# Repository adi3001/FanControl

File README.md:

# FanControl by CyberPlant

The a sample code for automatic speed control for the fan.
__________

# Description

Is, a compact device with a combination of some simple and useful functions.
The CyberPlant Automatic Fan Control measures temperature via the ds18b20 sensor.
the  temperature  sensor can be installed on the device or any other location
One single sensor can be connected directly to the device itself, or multiple sensors can be connected in series, for more precise ambient temperature reading. 
The CyberPlant Automatic Fan Control has offers smooth adjustments to the fan resolution speed. 
The combination of all the functions offer a precise versatile aid to controlling the temperature.

The fan motor takes its power directly from AC current running at 50Hz or 60Hz.

How does it work?
Setting up the CyberPlant Automatic Fan Control is very simple.

There are only two buttons required to set the programmable options.
With these, we can set the desired temperature values and also the Manual or Automatic Modes.

Automatic Mode.
During automatic mode if the temperature exceeds the set value, the electric charge will pulse every 2 seconds to add momentum.
If the temperature drops below the set value the fan speed will decrease until it stops. 
If the air temperature remains constant no change will occur.

This method allows the device to set the optimal speed for the fan, it prevents the temperature from exceeding the predetermined limit, reducing the total fan revolutions to the minimum possible and thereby saving on power consumption and noise levels.

On Manual Mode.
If you press the two buttons simultaneously the device will enter manual mode.
Here we can manually set the required power to the appliance and the settings are stored in non-volatile memory.
To switch back to automatic mode again just press both buttons simultaneously.

All logical parts are built on the ATmega328 microcontroller running the Arduino IDE. 
The Arduino board provides I2C Pins for connecting the device to other microcontrollers and a 6-pin to USB-TTL for easy program customisation which makes it all a very flexible and easily modifiable.to fit all your needs.
For example, maybe you would like to connect the device to the Internet this is easily done with the Arduino Internet Shield. 

or maybe you want the opposite, to heat the air in the room? It is easy! You can easily change the configuration of the device.

FanControl works with 220V AC and 110V AC at 50 Hz and 60 Hz And allows you to control the current to 4 amperes

It can display temperature in Celsius and Fahrenheit. 

FanControl is a simple and intuitive device with a great potential for modification and expansion. 
Use your imagination and a set of ready-made programs from Arduino IDE can build the automation of your dreams. 
This is an open source project. 

CyberPlant - help to people and love to plants

### Specifications

Temp sensor - DS18B20
Triac - 4A
works with 220V AC and 110V AC at 50 Hz and 60 Hz

[WWW.CYBERPLANT.INFO](http://www.cyberplant.info)

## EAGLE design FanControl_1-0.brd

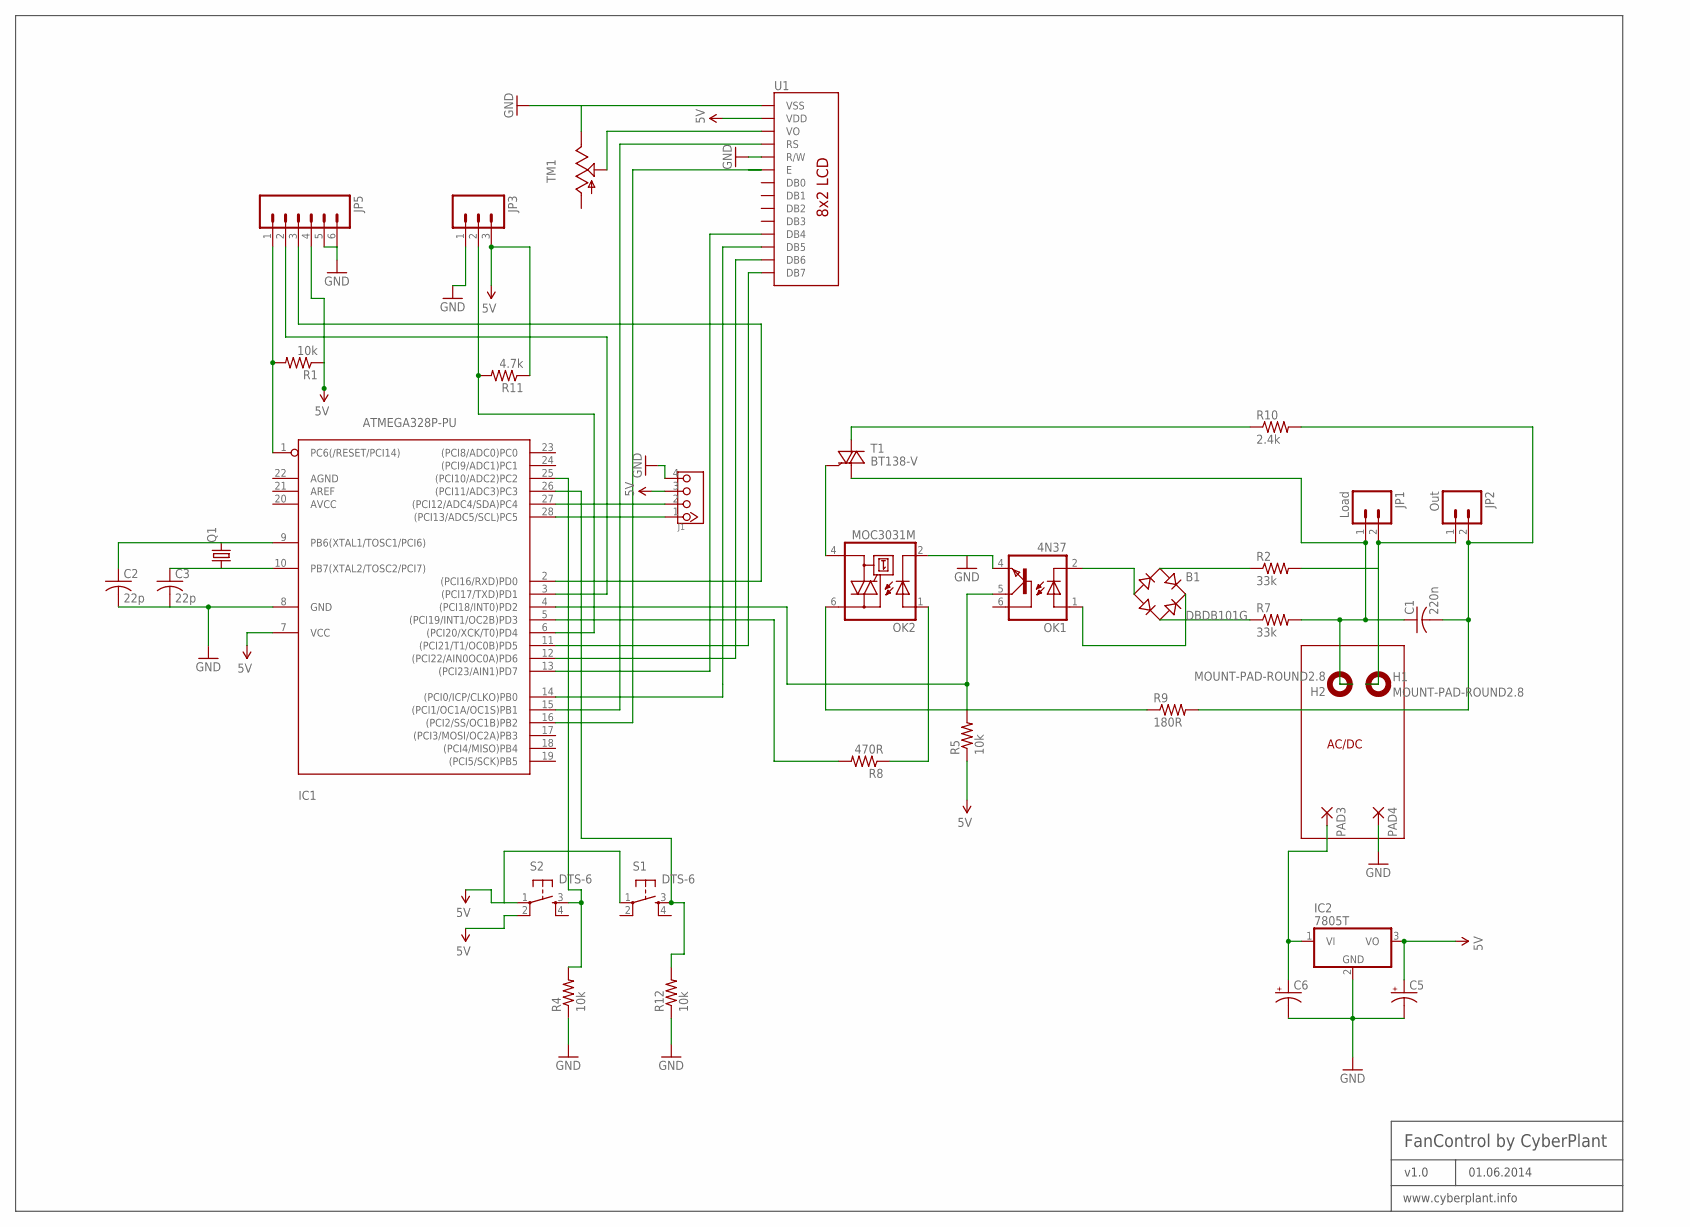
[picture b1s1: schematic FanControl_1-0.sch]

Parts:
B1: DBDB101G; DB
C1: 220n; C150-064X183
C2, C3: 22p; C050-025X075
C5, C6: CAP_POLPTH2; CPOL-RADIAL-10UF-25V
H1, H2: MOUNT-PAD-ROUND2.8; 2,8-PAD
IC1: ATMEGA328P-PU; DIL28-3
IC2: 7805T; TO220H
J1: TWIG-4P-2.090D; 4P-2.0-90D
JP1: Load; SCREWTERMINAL-5MM-2
JP2: Out; SCREWTERMINAL-5MM-2
JP3: M031X03_NO_SILK; 1X03_NO_SILK
JP5: M06SIP; 1X06
OK1: 4N37; DIL06
OK2: MOC3031M; DIL06
PAD3, PAD4: 1,6/0,8
Q1: CRYSTALHC49S; HC49/S
R1, R4, R5, R12: 10k; 1/6W-RES
R2, R7: 33k; AXIAL-0.6
R8: 470R; AXIAL-0.4
R9: 180R; AXIAL-0.8
R10: 2.4k; AXIAL-0.8
R11: 4.7k; AXIAL-0.4
S1, S2: DTS-6
T1: BT138-V; TO220BV
TM1: TRIM; 6MM
U1: LCD-8X2-WH0802A8X2; LCD-8X2-WH0802A

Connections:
5V: C5.1 (+), IC1.7 (VCC), IC2.3 (VO), J1.3, JP3.3, JP5.4, R1.1, R5.1, R11.P$1 (1), S1.1, S2.1, S2.2, U1.2 (VDD)
GND: C2.2, C3.2, C5.2 (-), C6.2 (-), IC1.8 (GND), IC2.2 (GND), J1.4, JP3.1, JP5.5, JP5.6, OK1.4 (EMI), OK2.2 (C), PAD4.1, R4.1, R12.1, TM1.E, U1.1 (VSS), U1.5 (R/W)
unnamed: C1.1, H2.B2,8, JP1.1, R7.P$2 (2), T1.T1 (A1)
unnamed: C1.2, JP2.2, R9.P$2 (2), R10.P$2 (2)
unnamed: H1.B2,8, JP1.2, JP2.1, R2.P$2 (2)
unnamed: B1.AC1, R2.P$1 (1)
unnamed: B1.AC2, R7.P$1 (1)
unnamed: B1.-, OK1.2 (C)
unnamed: B1.+, OK1.1 (A)
unnamed: IC1.4 ((PCI18/INT0)PD2), OK1.5 (COL), R5.2
unnamed: OK2.4 (A1), T1.G
unnamed: IC1.5 ((PCI19/INT1/OC2B)PD3), R8.P$2 (2)
unnamed: OK2.1 (A), R8.P$1 (1)
unnamed: R10.P$1 (1), T1.T2 (A2)
unnamed: OK2.6 (A2), R9.P$1 (1)
unnamed: C2.1, IC1.9 (PB6(XTAL1/TOSC1/PCI6)), Q1.2
unnamed: C3.1, IC1.10 (PB7(XTAL2/TOSC2/PCI7)), Q1.1
unnamed: IC1.6 ((PCI20/XCK/T0)PD4), JP3.2, R11.P$2 (2)
unnamed: C6.1 (+), IC2.1 (VI), PAD3.1
unnamed: TM1.S, U1.3 (VO)
unnamed: IC1.15 ((PCI1/OC1A/OC1S)PB1), U1.4 (RS)
unnamed: IC1.16 ((PCI2/SS/OC1B)PB2), U1.6 (E)
unnamed: IC1.13 ((PCI23/AIN1)PD7), U1.11 (DB4)
unnamed: IC1.14 ((PCI0/ICP/CLKO)PB0), U1.12 (DB5)
unnamed: IC1.12 ((PCI22/AIN0OC0A)PD6), U1.13 (DB6)
unnamed: IC1.11 ((PCI21/T1/OC0B)PD5), U1.14 (DB7)
unnamed: IC1.25 ((PCI10/ADC2)PC2), R4.2, S2.3
unnamed: IC1.26 ((PCI11/ADC3)PC3), R12.2, S1.3
unnamed: IC1.28 ((PCI13/ADC5/SCL)PC5), J1.1
unnamed: IC1.1 (PC6(/RESET/PCI14)), JP5.1, R1.2
unnamed: IC1.27 ((PCI12/ADC4/SDA)PC4), J1.2
unnamed: IC1.3 ((PCI17/TXD)PD1), JP5.2
unnamed: IC1.2 ((PCI16/RXD)PD0), JP5.3

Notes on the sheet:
AC/DC
FanControl by CyberPlant
v1.0
01.06.2014
www.cyberplant.info

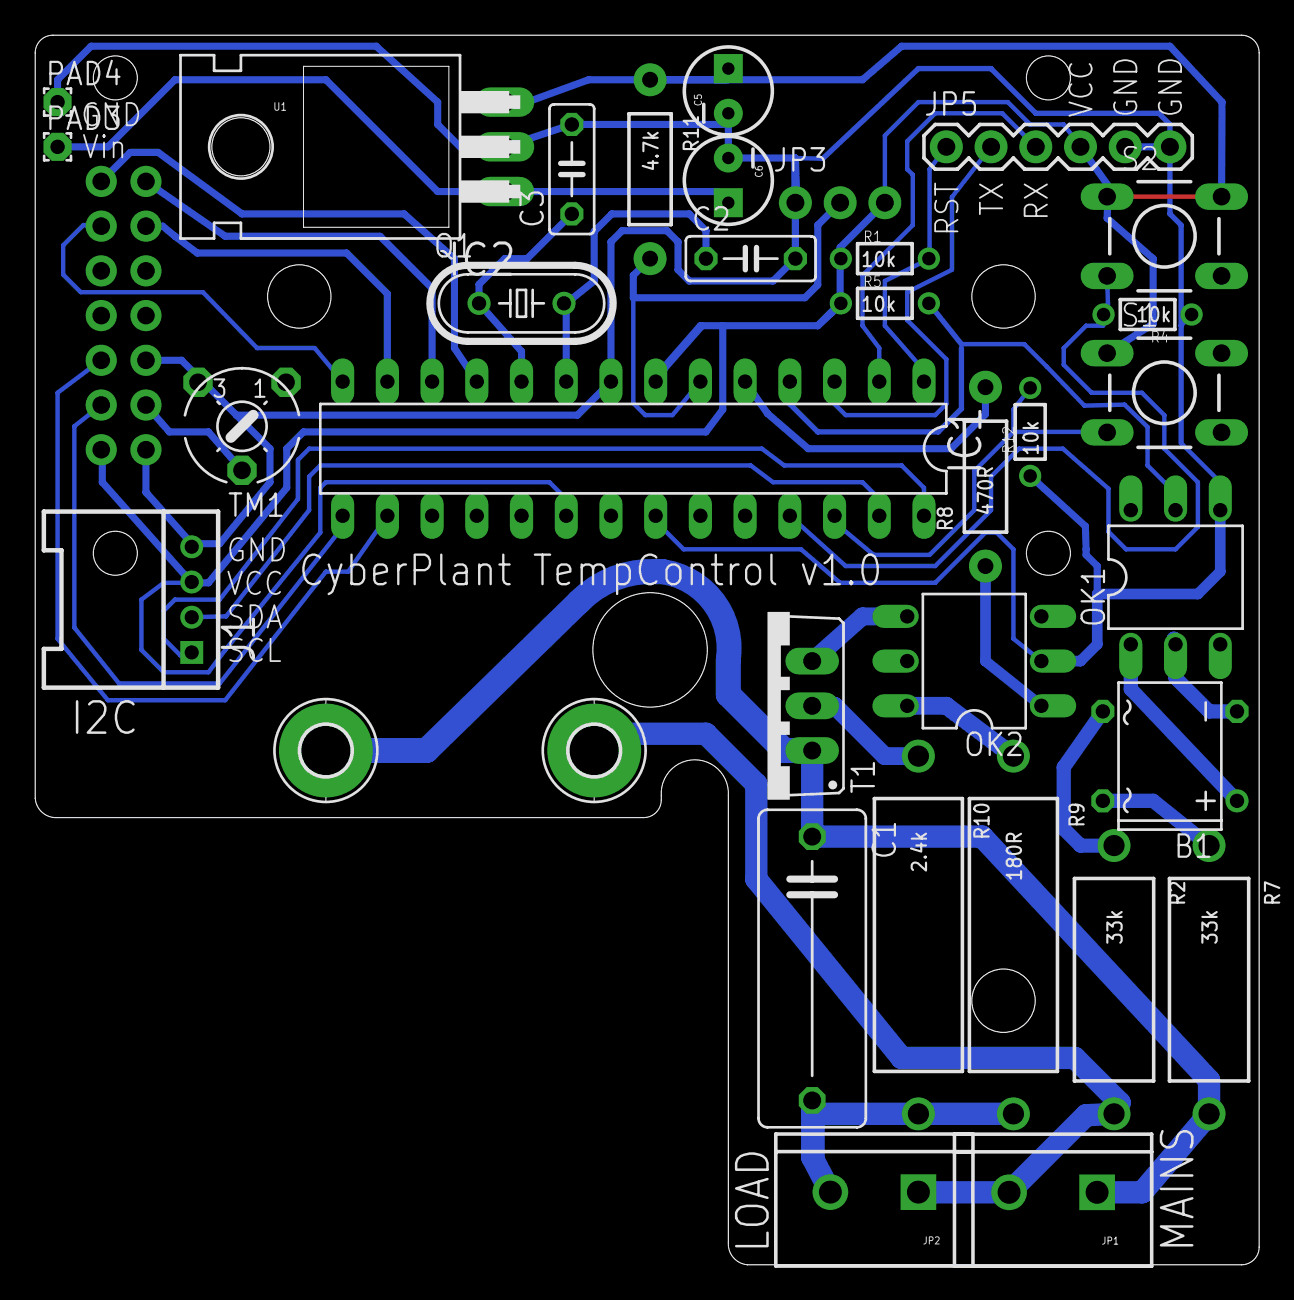
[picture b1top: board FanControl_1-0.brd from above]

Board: 2 copper layers, 69.5 x 69.8 mm, 35 parts (0 on the bottom side), 33 nets.

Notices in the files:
parts and their libraries:
wh0802a2: Licensing: CC v3.0 Share-Alike You are welcome to use this library for commercial purposes.
